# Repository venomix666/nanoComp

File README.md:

Simple carrier board for the Tang Nano 20K, intended for computer applications.   

The following features interfaces are available:
* USB-C power input with diode protection to avoid back-powering when Tang Nano 20K USB cable is connected
* On/Off switch
* Power LED
* Two USB type A ports.
* UART header for FTDI TTL-232R-3V3 cable
* GPIO header
* Power header with 5V and 3V3 available

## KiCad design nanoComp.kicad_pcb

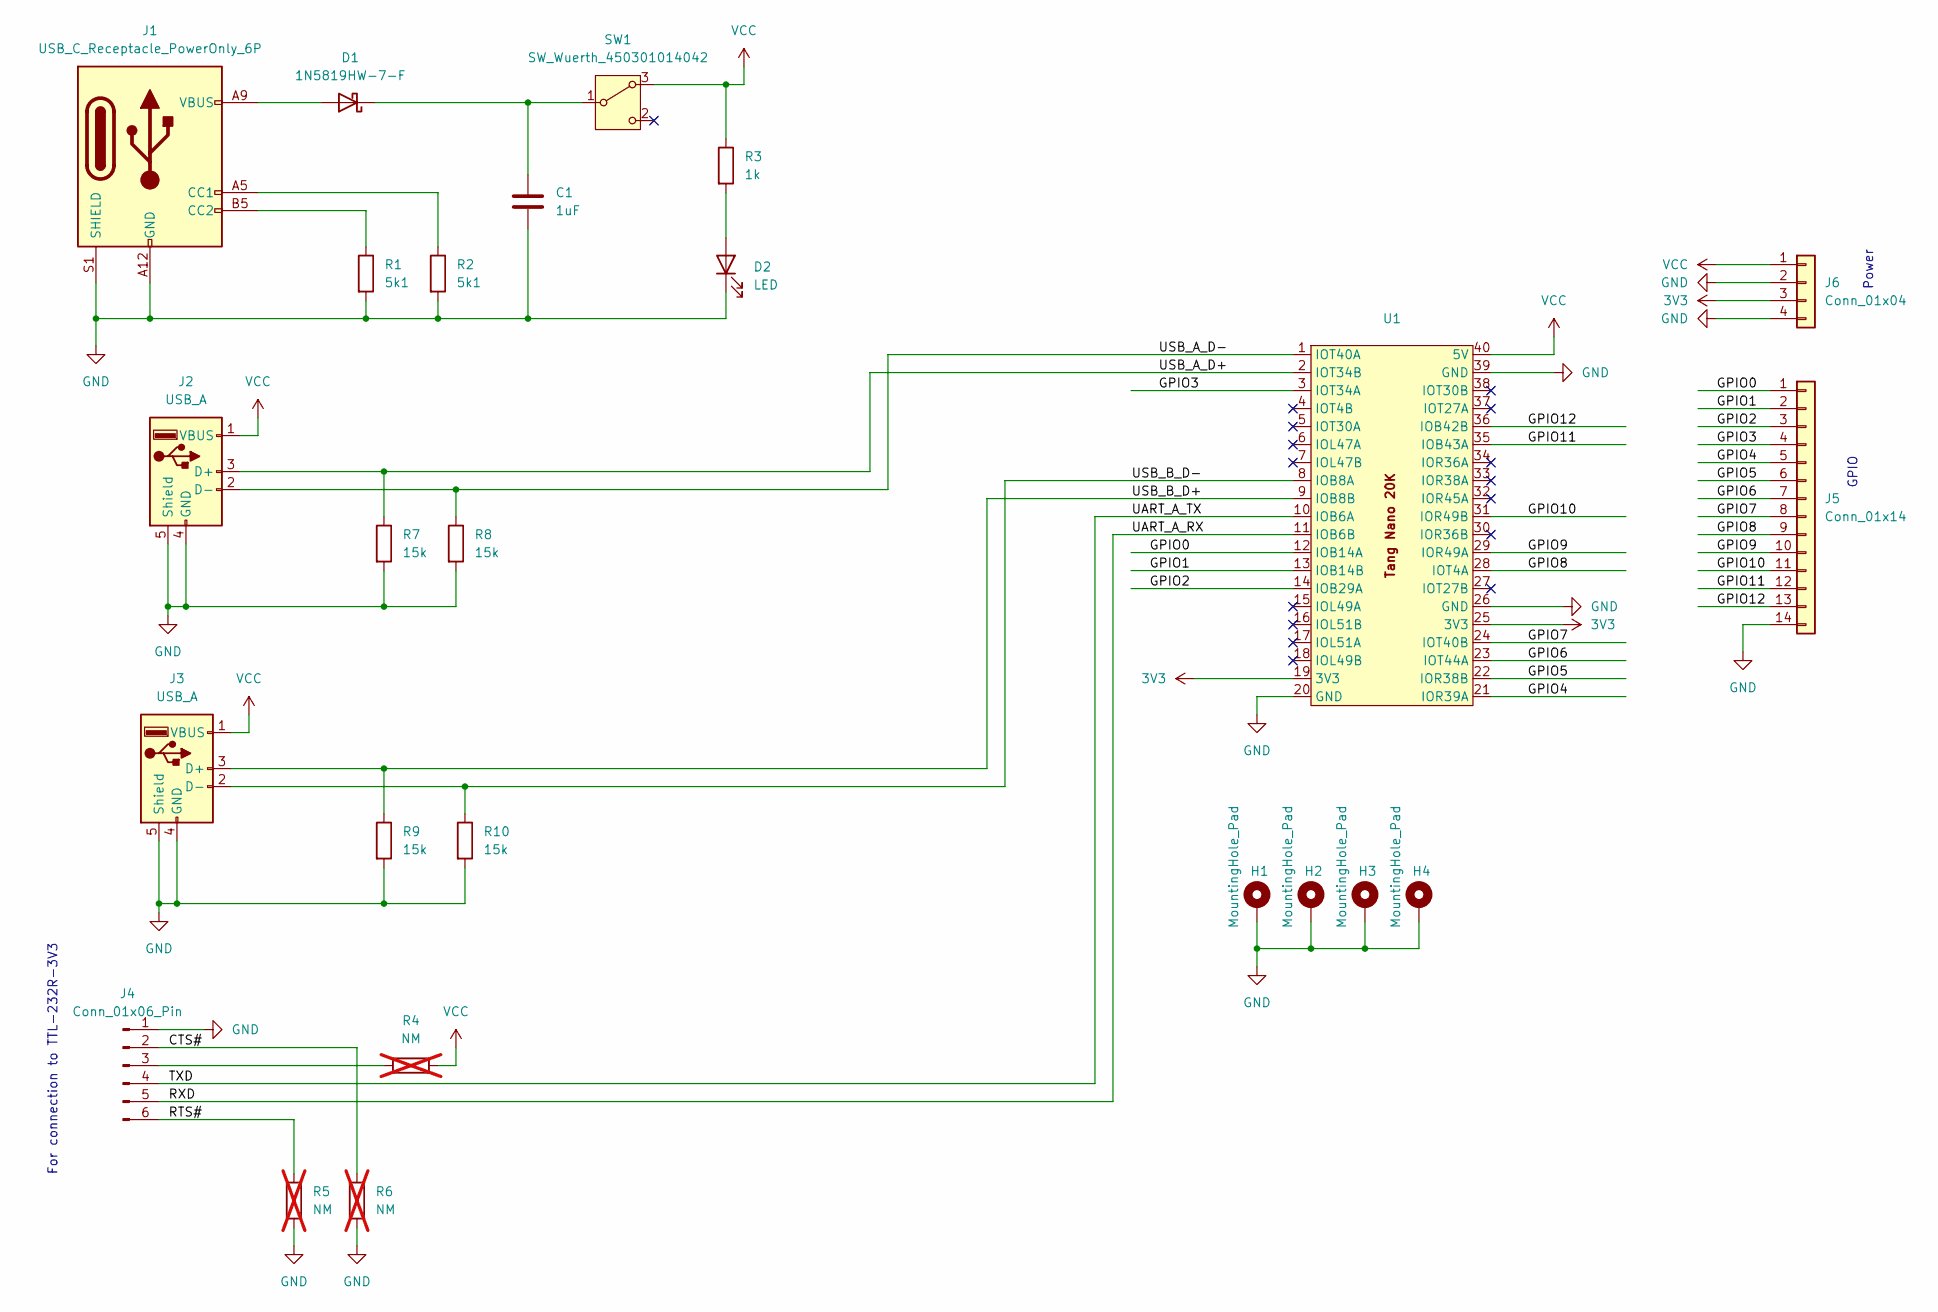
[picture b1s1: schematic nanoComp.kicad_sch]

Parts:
C1: 1uF; C_0805_2012Metric_Pad1.18x1.45mm_HandSolder
D1: 1N5819HW-7-F; D_SOD-123; Manufacturer P/N 1N5819HW-7-F
D2: LED; LED_0805_2012Metric_Pad1.15x1.40mm_HandSolder; Manufacturer P/N SM0805UGC
H1, H2, H3, H4: MountingHole_Pad; MountingHole_3.2mm_M3_ISO7380_Pad
J1: USB_C_Receptacle_PowerOnly_6P; USB_C_Receptacle_GCT_USB4125-xx-x-0190_6P_TopMnt_Horizontal; Manufacturer P/N USB4125-GF-A
J2, J3: USB_A; USB_A_Molex_67643_Horizontal; Manufacturer P/N 67643-3910
J4: Conn_01x06_Pin; PinHeader_1x06_P2.54mm_Vertical
J5: Conn_01x14; PinHeader_1x14_P2.54mm_Vertical
J6: Conn_01x04; PinHeader_1x04_P2.54mm_Vertical
R1, R2: 5k1; R_0805_2012Metric
R3: 1k; R_0805_2012Metric
R4, R5, R6: NM; R_0805_2012Metric; not fitted
R7, R8, R9, R10: 15k; R_0805_2012Metric
SW1: SW_Wuerth_450301014042; SW_Slide-03_Wuerth-WS-SLTV_10x2.5x6.4_P2.54mm; Manufacturer P/N 450301014042
U1: tangnano20k

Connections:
3V3: J6.3, U1.19 (3V3), U1.25 (3V3)
/CTS#: J4.2, R6.2
/GPIO0: J5.1, U1.12 (IOB14A)
/GPIO1: J5.2, U1.13 (IOB14B)
/GPIO2: J5.3, U1.14 (IOB29A)
/GPIO3: J5.4, U1.3 (IOT34A)
/GPIO4: J5.5, U1.21 (IOR39A)
/GPIO5: J5.6, U1.22 (IOR38B)
/GPIO6: J5.7, U1.23 (IOT44A)
/GPIO7: J5.8, U1.24 (IOT40B)
/GPIO8: J5.9, U1.28 (IOT4A)
/GPIO9: J5.10, U1.29 (IOR49A)
/GPIO10: J5.11, U1.31 (IOR49B)
/GPIO11: J5.12, U1.35 (IOB43A)
/GPIO12: J5.13, U1.36 (IOB42B)
/RTS#: J4.6, R5.2
/RXD: J4.5, U1.11 (IOB6B)
/TXD: J4.4, U1.10 (IOB6A)
/USB_A_D+: J2.3 (D+), R7.1, U1.2 (IOT34B)
/USB_A_D-: J2.2 (D-), R8.1, U1.1 (IOT40A)
/USB_B_D+: J3.3 (D+), R9.1, U1.9 (IOB8B)
/USB_B_D-: J3.2 (D-), R10.1, U1.8 (IOB8A)
GND: C1.2, D2.1 (K), H1.1, H2.1, H3.1, H4.1, J1.A12 (GND), J1.B12 (GND), J1.S1 (SHIELD), J2.4 (GND), J2.5 (Shield), J3.4 (GND), J3.5 (Shield), J4.1, J5.14, J6.2, J6.4, R1.2, R2.2, R5.1, R6.1, R7.2, R8.2, R9.2, R10.2, U1.20 (GND), U1.26 (GND), U1.39 (GND)
unnamed: D1.2 (A), J1.A9 (VBUS), J1.B9 (VBUS)
unnamed: C1.1, D1.1 (K), SW1.1 (B)
unnamed: D2.2 (A), R3.2
unnamed: J1.A5 (CC1), R2.1
unnamed: J1.B5 (CC2), R1.1
unnamed: J4.3, R4.1
VCC: J2.1 (VBUS), J3.1 (VBUS), J6.1, R3.1, R4.2, SW1.3 (A), U1.40 (5V)

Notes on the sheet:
For connection to TTL-232R-3V3
GPIO
Power

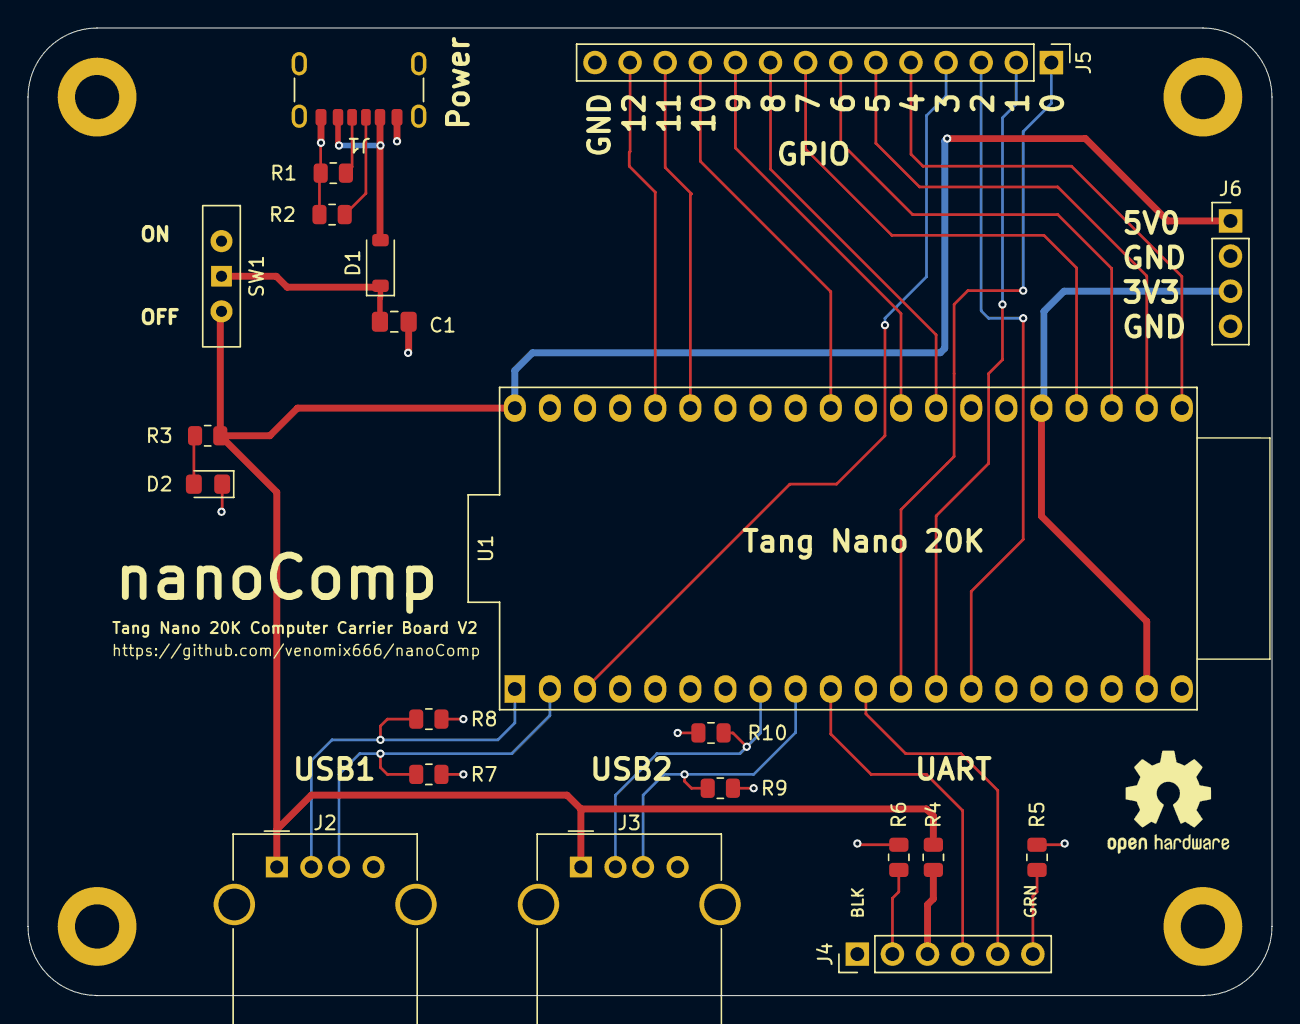
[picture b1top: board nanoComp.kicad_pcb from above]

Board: 2 copper layers, 90.0 x 70.0 mm, 25 parts (0 on the bottom side), 30 nets.

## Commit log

2024-07-10 Initial commit of board, more or less ready
2024-07-10 Added PDF schematics
2024-07-15 Finishing touches + manufacturing files
2024-07-15 Schematics cleanup
2024-07-16 Added step model of Tang Nano 20K board + rendered image of board
2024-07-16 Cropped 3D image
2024-07-16 Added 3D model for power switch and updated board image
2024-07-16 Added assembly drawing
2024-07-25 Added 15k pulldowns on USB data lines for master configuration
2024-07-26 Updated assembly drawing and added 3D model of board
2024-07-26 Added photo, moved image files to separate folder
